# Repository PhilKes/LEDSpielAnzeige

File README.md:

# LEDSpielAnzeige - Controller for LED Scoreboard

 ### Display
 * 2 x 8 7-Segment Displays
 * Eacg Segment 7 LEDs in Series (Vfor=1.9V)
 * Center Segments 8 LEDs in Series
 * All Anodes (+) of the same Segments connected (all SegA,...) (Data)
 * LEDs of a single 7-Segment Display have a common Cathode (-) (Address)
 * DecimalPoint connections for ":",">","|",...
 
 ### Connections
  
 * 2x 16Pin Cable connections
 * 8 Pin Address (only a single Bit "1" at a time)
 * 8 Pin Data (7-Segments)
 * Addresses are multiplexed
 
 ### Schematic
 
  ---
 ### Board
 
 [Mirrored Image for Soldering](./doc/eagle/LEDAnzeige_Multiplexing_Board_mirror.png)
 ---
 #### Parts
  * [LM2596 Step-Down DC Buck Converter](https://www.reichelt.de/schaltregler-step-down-adj-3a-4-75-40vi-to220-5-lm2596tvadj-p255435.html?&trstct=pos_7&nbc=1)
  * [IC Sockel 14/16pin](https://www.reichelt.de/ic-sockel-16-polig-doppelter-federkontakt-gs-16-p8208.html?&nbc=1)
  * [Perboard 16x10cm](https://www.reichelt.de/lochrasterplatine-hartpapier-160x100mm-h25pr160-p8272.html?&nbc=1)
  * [WeMos D1 mini](https://www.ebay.de/itm/D1Mini-ESP8266-Modul-Mikrokontroller-Board-WLAN-Wifi-Nodemcu-Wemos-Arduino/164007576934?ssPageName=STRK%3AMEBIDX%3AIT&_trksid=p2057872.m2749.l2649)
  * [DCAdapter 24V](https://www.reichelt.de/steckernetzteil-25-w-24-v-1-04-a-mw-gst25e24-p171101.html?&nbc=1)
#### Drivers
 * [UDN 2981(=_TD62783AP_)  Source Driver](https://www.reichelt.de/leistungstreiber-8-kanal-dil-18-udn-2981-p22008.html?&trstct=pos_0&nbc=1)
 * [ULN2803 NPN Darlington Arrays](https://www.reichelt.de/eight-darlington-arrays-dil-18-uln-2803a-p22085.html?&trstct=pos_0&nbc=1)
 * [74HC595 Shift Register](https://www.reichelt.de/shift-register-3-state-ausgang-2-6-v-dil-16-74hc-595-p3269.html?&trstct=pos_0&nbc=1)
 ---
 
 # Code
 
 ### Wemos Arduino Sketch
 * **Multiplexing** both Addressbusses (**Common Cathodes**) (_ULN2803s_ "B1-B8"+"C1-C8") with 1x _74HC595_ ("U2") output
 * Loading **7-Segment Data** (**Anodes**) for every Display concurrent to multiplexing with 2x _74HC595_ ("U1"+"U3")
 * Switch modes on **WiFi** commands
 
 ### React Web App
 * **WebServer** for User Interface
 * Sending Commands over WiFi
 * [ESP8266-React Framework](https://github.com/rjwats/esp8266-react)
 ---
 ### Links
 * [ULN2803 Function](https://www.conrad.de/de/ratgeber/handwerk-industrie-wiki/elektronik-bauteile/uln2803.html#anschluss)
 * [Arduino Forum Thread](https://forum.arduino.cc/index.php?topic=688158.0)

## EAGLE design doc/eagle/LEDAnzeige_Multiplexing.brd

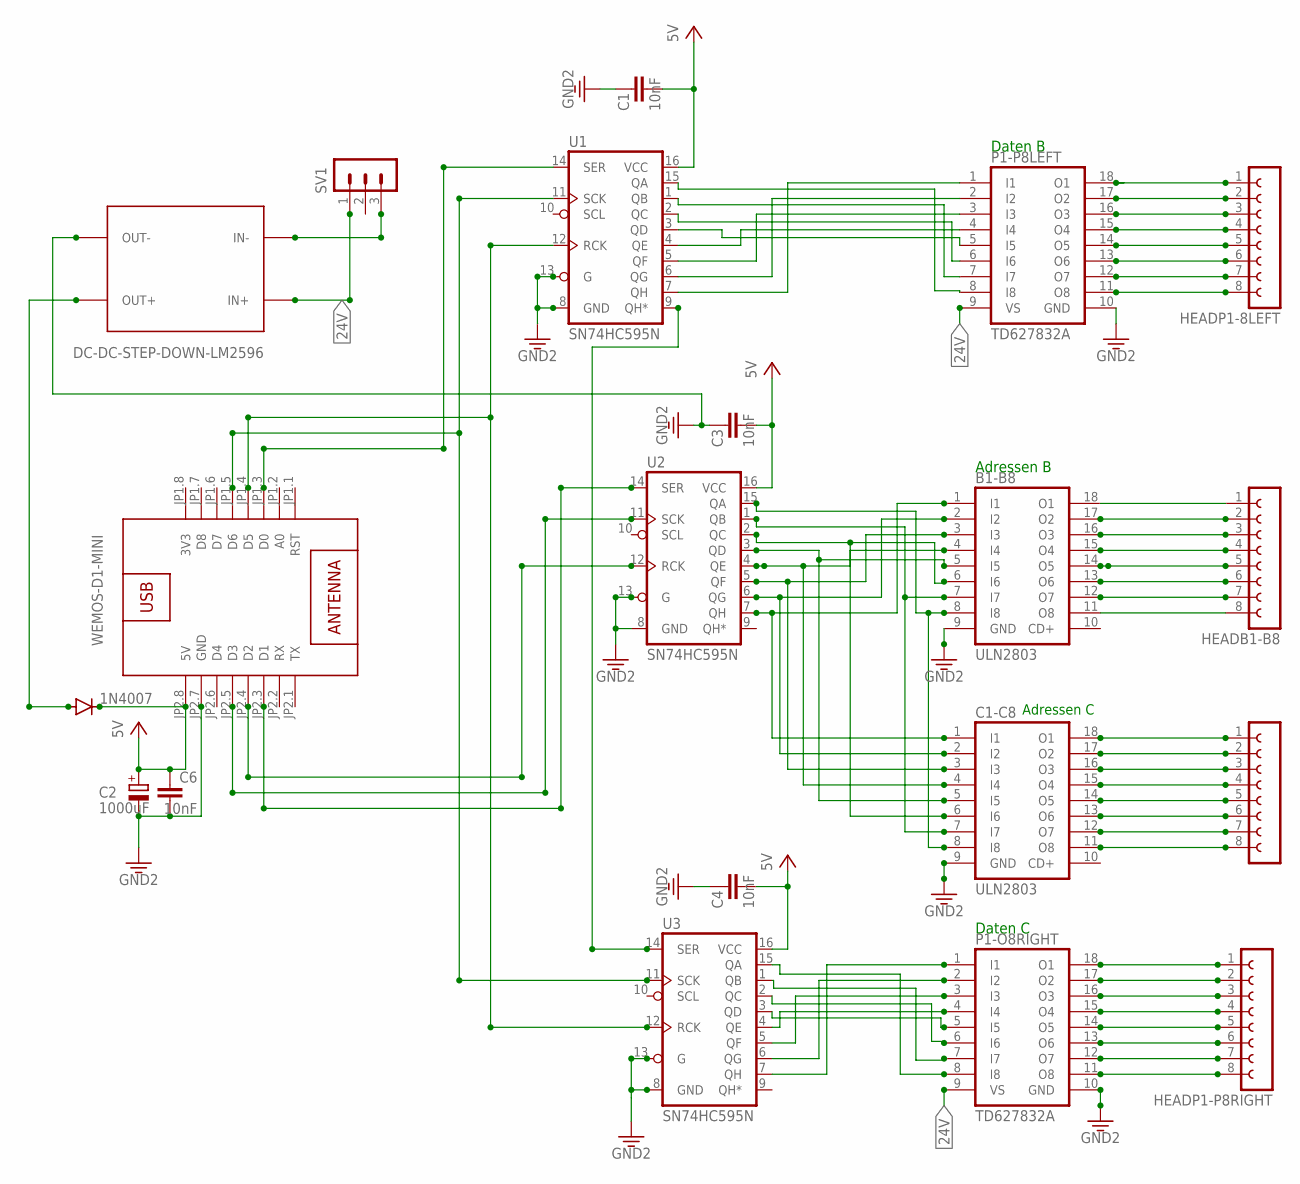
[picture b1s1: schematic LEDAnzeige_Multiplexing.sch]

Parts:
1N4007: DIODE-D-2.5; D-2.5
B1-B8: ULN2803; DIL18
C1, C3, C4, C6: 10nF; C025-025X050
C1-C8: ULN2803; DIL18
C2: 1000uF; E5-10,5
HEADB1-B8: FE08-1; FE08
HEADC1-C8: FE08-1; FE08
HEADP1-8LEFT, HEADP1-P8RIGHT: FE08-1; FE08
P1-O8RIGHT, P1-P8LEFT: TD627832A; DIL18
SV1: MA03-1
U1, U2, U3: SN74HC595N; DIP16
U$1: WEMOS-D1-MINI
U$2: DC-DC-STEP-DOWN-LM2596

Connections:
3V3: U$1.JP1.8 (3V3)
24V: P1-O8RIGHT.9 (VS), P1-P8LEFT.9 (VS), SV1.1, U$2.IN+
GND: B1-B8.9 (GND), C1.1, C1-C8.9 (GND), C2.-, C3.1, C4.1, C6.2, P1-O8RIGHT.10 (GND), P1-P8LEFT.10 (GND), U1.8 (GND), U1.13 (G), U2.8 (GND), U2.13 (G), U3.8 (GND), U3.13 (G), U$1.JP2.7 (GND), U$2.OUT-
unnamed: B1-B8.7 (I7), C1-C8.7 (I7), U2.1 (QB)
unnamed: B1-B8.2 (I2), C1-C8.2 (I2), U2.6 (QG)
unnamed: B1-B8.3 (I3), C1-C8.3 (I3), U2.5 (QF)
unnamed: B1-B8.4 (I4), C1-C8.4 (I4), U2.4 (QE)
unnamed: B1-B8.5 (I5), C1-C8.5 (I5), U2.3 (QD)
unnamed: B1-B8.6 (I6), C1-C8.6 (I6), U2.2 (QC)
unnamed: B1-B8.1 (I1), C1-C8.1 (I1), U2.7 (QH)
unnamed: B1-B8.8 (I8), C1-C8.8 (I8), U2.15 (QA)
unnamed: HEADP1-8LEFT.2, P1-P8LEFT.17 (O2)
unnamed: HEADP1-8LEFT.3, P1-P8LEFT.16 (O3)
unnamed: HEADP1-8LEFT.4, P1-P8LEFT.15 (O4)
unnamed: HEADP1-8LEFT.5, P1-P8LEFT.14 (O5)
unnamed: HEADP1-8LEFT.6, P1-P8LEFT.13 (O6)
unnamed: HEADP1-8LEFT.7, P1-P8LEFT.12 (O7)
unnamed: HEADP1-8LEFT.8, P1-P8LEFT.11 (O8)
unnamed: B1-B8.18 (O1), HEADB1-B8.1
unnamed: B1-B8.17 (O2), HEADB1-B8.2
unnamed: B1-B8.16 (O3), HEADB1-B8.3
unnamed: B1-B8.15 (O4), HEADB1-B8.4
unnamed: HEADP1-8LEFT.1, P1-P8LEFT.18 (O1)
unnamed: B1-B8.14 (O5), HEADB1-B8.5
unnamed: B1-B8.13 (O6), HEADB1-B8.6
unnamed: B1-B8.12 (O7), HEADB1-B8.7
unnamed: B1-B8.11 (O8), HEADB1-B8.8
unnamed: P1-P8LEFT.1 (I1), U1.7 (QH)
unnamed: HEADP1-P8RIGHT.1, P1-O8RIGHT.18 (O1)
unnamed: P1-P8LEFT.2 (I2), U1.6 (QG)
unnamed: HEADP1-P8RIGHT.3, P1-O8RIGHT.16 (O3)
unnamed: P1-P8LEFT.3 (I3), U1.5 (QF)
unnamed: HEADP1-P8RIGHT.2, P1-O8RIGHT.17 (O2)
unnamed: P1-P8LEFT.4 (I4), U1.4 (QE)
unnamed: P1-P8LEFT.5 (I5), U1.3 (QD)
unnamed: HEADP1-P8RIGHT.5, P1-O8RIGHT.14 (O5)
unnamed: U1.14 (SER), U$1.JP1.3 (D0)
unnamed: HEADP1-P8RIGHT.6, P1-O8RIGHT.13 (O6)
unnamed: U2.14 (SER), U$1.JP2.3 (D1)
unnamed: HEADP1-P8RIGHT.4, P1-O8RIGHT.15 (O4)
unnamed: HEADP1-P8RIGHT.7, P1-O8RIGHT.12 (O7)
unnamed: P1-P8LEFT.6 (I6), U1.2 (QC)
unnamed: P1-P8LEFT.7 (I7), U1.1 (QB)
unnamed: P1-P8LEFT.8 (I8), U1.15 (QA)
unnamed: P1-O8RIGHT.2 (I2), U3.6 (QG)
unnamed: P1-O8RIGHT.3 (I3), U3.5 (QF)
unnamed: P1-O8RIGHT.4 (I4), U3.4 (QE)
unnamed: P1-O8RIGHT.5 (I5), U3.3 (QD)
unnamed: P1-O8RIGHT.6 (I6), U3.2 (QC)
unnamed: HEADP1-P8RIGHT.8, P1-O8RIGHT.11 (O8)
unnamed: C1-C8.18 (O1), HEADC1-C8.1
unnamed: C1-C8.17 (O2), HEADC1-C8.2
unnamed: C1-C8.16 (O3), HEADC1-C8.3
unnamed: C1-C8.15 (O4), HEADC1-C8.4
unnamed: C1-C8.14 (O5), HEADC1-C8.5
unnamed: P1-O8RIGHT.7 (I7), U3.1 (QB)
unnamed: P1-O8RIGHT.8 (I8), U3.15 (QA)
unnamed: C1-C8.13 (O6), HEADC1-C8.6
unnamed: C1-C8.12 (O7), HEADC1-C8.7
unnamed: C1-C8.11 (O8), HEADC1-C8.8
unnamed: U2.12 (RCK), U$1.JP2.4 (D2)
unnamed: SV1.3, U$2.IN-
unnamed: 1N4007.A, U$2.OUT+
unnamed: P1-O8RIGHT.1 (I1), U3.7 (QH)
unnamed: U1.12 (RCK), U3.12 (RCK), U$1.JP1.4 (D5)
unnamed: U1.11 (SCK), U3.11 (SCK), U$1.JP1.5 (D6)
unnamed: U2.11 (SCK), U$1.JP2.5 (D3)
unnamed: U1.9 (QH*), U3.14 (SER)
VCC: 1N4007.C, C1.2, C2.+, C3.2, C4.2, C6.1, U1.16 (VCC), U2.16 (VCC), U3.16 (VCC), U$1.JP2.8 (5V)

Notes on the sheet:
Daten B
Daten C
Adressen B
Adressen C

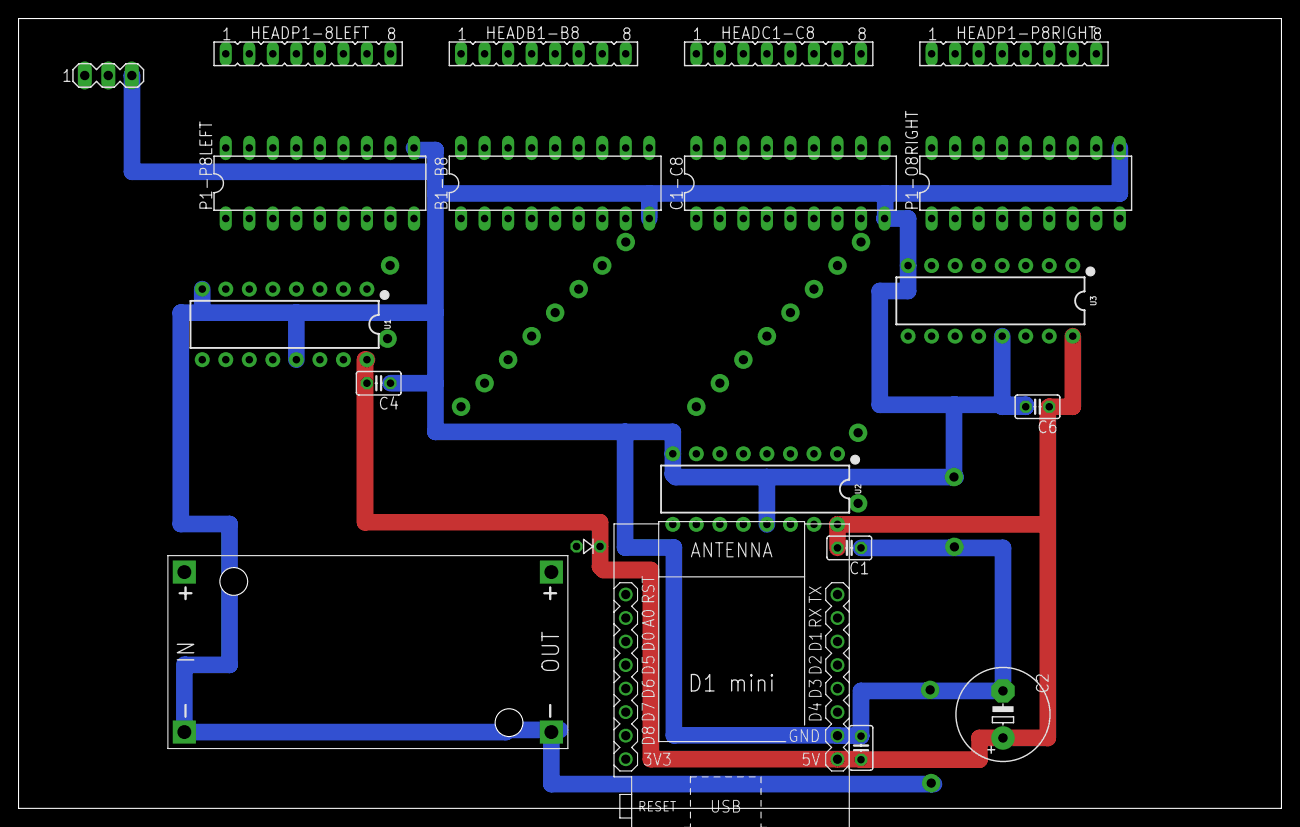
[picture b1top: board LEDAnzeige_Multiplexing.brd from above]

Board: 8 copper layers, 136.3 x 85.3 mm, 20 parts (0 on the bottom side), 68 nets.

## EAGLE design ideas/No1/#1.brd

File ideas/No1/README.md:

- Multiplexing cathode.
- Use two 74HC595 Shift Register for cathode and anode.
- Use UDN2981 for source.
- Use ULN2803 for drain.
 
 ### Schaltplan

 #### Bauteile
 
 ### Links

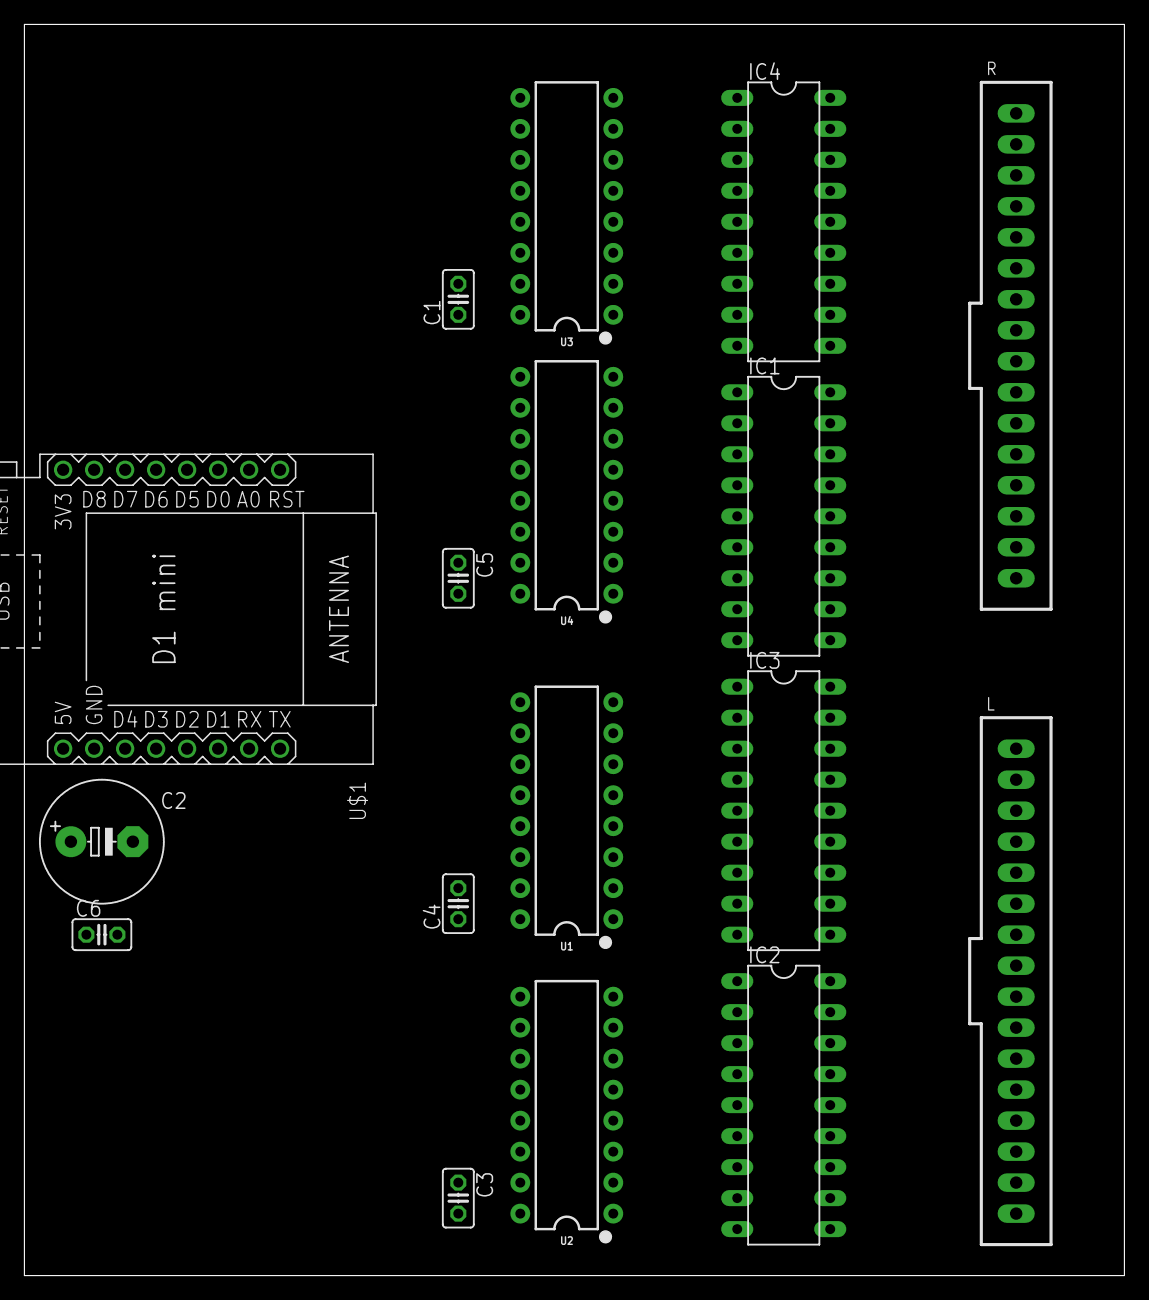
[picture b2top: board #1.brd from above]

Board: 2 copper layers, 90.2 x 102.5 mm, 17 parts (0 on the bottom side), 74 nets, no tracks yet.

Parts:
C1, C3, C4, C5, C6: 10nF; C025-025X050
C2: 1000uF; E5-10,5
IC1, IC2: ULN2803; DIL18
IC3, IC4: TD620831A; DIL18
L: C-GRID-16-70543; 70543-16
R: C-GRID-16-70543; 70543-16
U1, U2, U3, U4: SN74HC595N; DIP16
U$1: WEMOS-D1-MINI

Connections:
3.3V: C1.1, C2.-, C3.1, C4.1, C5.1, C6.2, IC1.9, IC2.9, IC3.10, IC4.10, U1.8, U2.8, U3.8, U4.8, U$1.JP2.7
unnamed: IC2.1, U2.15
unnamed: IC2.2, U2.1
unnamed: IC2.3, U2.2
unnamed: IC2.4, U2.3
unnamed: IC2.5, U2.4
unnamed: IC2.6, U2.5
unnamed: IC2.7, U2.6
unnamed: IC2.8, U2.7
unnamed: IC3.18, L.1
unnamed: IC3.17, L.2
unnamed: IC3.16, L.3
unnamed: IC3.15, L.4
unnamed: IC3.14, L.5
unnamed: IC3.13, L.6
unnamed: IC3.12, L.7
unnamed: IC3.11, L.8
unnamed: IC2.11, L.16
unnamed: IC2.12, L.15
unnamed: IC2.13, L.14
unnamed: IC2.14, L.13
unnamed: IC2.15, L.12
unnamed: IC2.16, L.11
unnamed: IC2.17, L.10
unnamed: IC2.18, L.9
unnamed: IC4.17, R.2
unnamed: IC4.15, R.4
unnamed: IC4.13, R.6
unnamed: IC3.8, U1.7
unnamed: IC4.11, R.8
unnamed: U1.14, U$1.JP1.5
unnamed: IC4.8, U3.7
unnamed: U1.12, U3.12, U$1.JP1.4
unnamed: U2.14, U$1.JP2.5
unnamed: U2.12, U4.12, U$1.JP2.3
unnamed: IC1.11, R.16
unnamed: IC1.12, R.15
unnamed: IC3.1, U1.15
unnamed: IC3.2, U1.1
unnamed: IC3.3, U1.2
unnamed: IC3.4, U1.3
unnamed: IC3.5, U1.4
unnamed: IC4.6, U3.5
unnamed: IC3.7, U1.6
unnamed: IC3.6, U1.5
unnamed: IC1.13, R.14
unnamed: IC1.14, R.13
unnamed: IC1.15, R.12
unnamed: IC1.16, R.11
unnamed: IC1.17, R.10
unnamed: IC1.18, R.9
unnamed: IC4.18, R.1
unnamed: IC4.16, R.3
unnamed: IC4.14, R.5
unnamed: IC4.12, R.7
unnamed: IC4.1, U3.15
unnamed: IC4.2, U3.1
unnamed: IC4.3, U3.2
unnamed: IC4.4, U3.3
unnamed: IC4.5, U3.4
unnamed: U2.9, U4.14
unnamed: IC4.7, U3.6
unnamed: U1.11, U3.11, U$1.JP1.3
unnamed: U2.11, U4.11, U$1.JP2.4
unnamed: IC1.1, U4.15
unnamed: IC1.2, U4.1
unnamed: IC1.3, U4.2
unnamed: IC1.4, U4.3
unnamed: IC1.5, U4.4
unnamed: IC1.6, U4.5
unnamed: IC1.7, U4.6
unnamed: IC1.8, U4.7
unnamed: U1.9, U3.14
VCC: C1.2, C2.+, C3.2, C4.2, C5.2, C6.1, IC3.9, IC4.9, U1.16, U2.16, U3.16, U4.16, U$1.JP2.8

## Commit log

2020-06-02 README.md updated
2020-06-02 Eagle Schematic added
2020-06-02 Test Sketch für MAX7219 + Transistoren added
2020-06-03 score_anzeige.pdf
2020-06-03 hallo
2020-06-03 tschüüüüüs
2020-06-04 Schematic fixed
2020-06-04 Test Schematic updated
2020-06-04 test 2k2Ohm ansatt 220
2020-06-05 Bauteilliste updated
2020-06-05 new idea #1
2020-06-05 update idea #1
2020-06-06 ides/no1 Schematic
2020-06-06 Kabel Pinout PNG
2020-06-06 picture with cable pins
2020-06-06 update picture with cable pins
2020-06-07 1_route_1register.sch
2020-06-07 1_route_1register.sch updated
2020-06-08 1_route_1register.sch changed
2020-06-11 Schematic updated + Refactoring
2020-06-11 Board added
2020-06-11 Mirrored Boardimage for Soldering added
2020-06-11 test/wemos_sketch updated
2020-06-12 Board updated
2020-06-13 wemos_serial_sketch added
2020-06-13 wemo_sketch updated
2020-06-14 /wemos PlatformIO project added
2020-06-14 README updated
2020-06-14 WiFi + OTA enable
2020-06-14 wifi_settings.h added
2020-06-14 ignore wifi_settings.h
2020-06-14 added time client
2020-06-15 Added clock and temperature display
2020-06-16 added home and guest score board support
2020-06-16 Added web interface for control and score settings
2020-06-17 Added kabu play mode4 players
2020-06-19 added dimmer
2020-06-19 Added daylightsaving, optimised code with returns and calls
2020-06-20 wemos_react_platformio Project added
2020-06-20 LEDScoreboardService with wemos_sketch
2020-06-21 Add NTPStatus to LEDScoreboardService + default wemosLoop show current LocalTime test
2020-06-22 added comments and changed time to avoid flickering

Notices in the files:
parts and their libraries:
diy-modules: Released under the Creative Commons Attribution 4.0 International License: http://creativecommons.org/licenses/by/4.0
SparkFun-IC-Logic: Licensing: Creative Commons ShareAlike 4.0 International - https://creativecommons.org/licenses/by-sa/4.0
